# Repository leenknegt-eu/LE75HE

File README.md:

# LE75HE

LE75HE is a 75-key Hall-effect keyboard PCB in the XD75 form factor (15 × 5 grid, all 1U), running [libhmk](https://github.com/peppapighs/libhmk) firmware with 8 kHz polling.

## Status

- Work in progress. PCB and plate are routed but **not yet fabricated or verified**.
- Firmware definition is generated from the PCB netlist and passes the libhmk schema check; it is untested on hardware.

## Layout

Alphanumerics and modifiers sit in the left (columns 1–6) and right (columns 10–15) blocks. The three centre columns hold `-` `` ` `` `=`, `[` `\` `]`, Home/Del/PgUp, End/↑/PgDn and ←/↓/→. Source: [`keyboard-layout.json`](keyboard-layout.json) ([keyboard-layout-editor.com](http://www.keyboard-layout-editor.com)).

### Fn layer (default)

| Key        | Fn            | Key           | Fn                 |
| ---------- | ------------- | ------------- | ------------------ |
| 1–5, 6–0   | F1–F5, F6–F10 | Home / Del / PgUp | Ins / – / Vol+ |
| `-` / `=`  | F11 / F12     | ↑ / PgDn      | Mute / Vol−        |
| Backspace  | Delete        | ← / ↓ / →     | Prev / Play / Next |
| `[` `\` `]`| PrtSc / ScrLk / Pause | U / I / O / P | Profile 0–3 |
| `'`        | Bootloader    | Enter         | Profile swap       |

Layers 2–3 are empty. Everything is remappable in [hmkconf](https://hmk.prasertsuk.com) without reflashing.

## Hardware

| Function        | Part                         | Designator |
| --------------- | ---------------------------- | ---------- |
| MCU             | AT32F405RCT7 (LQFP-64)       | U4         |
| Crystal         | 12 MHz, X322512MSB4SI, 2 × 30 pF | Y1, C152, C153 |
| Hall sensors    | 75 × DRV5055A3 (SOT-23-3), see below | HE1–HE75 |
| Analog muxes    | 10 × SN74LV4051A (TSSOP-16)  | AM1–AM10   |
| LDO, digital    | TLV75733PDYDR, 3.3 V         | U6 (+3.3V) |
| LDO, analog     | TLV75733PDYDR, 3.3 V         | U5 (+3.3VA, sensors + muxes) |
| USB-C           | HRO TYPE-C-31-M-12, CC 2 × 5.1 kΩ | J1, R1, R2 |
| Alt. USB input  | JST SH 1.0 mm 4-pin (VBUS, D−, D+, GND) | J2 |
| ESD             | USBLC6-2SC6                  | U1         |
| Fuse            | BSMD0805-050-24V (500 mA hold) | F1       |
| Reset / Boot    | TS-1187A tactile switches    | SW1 (NRST), SW2 (BOOT0) |
| BOOT0 pull-down | 12 kΩ                        | R4         |
| USB HS bias     | 12 kΩ to GND on OTGHS1_R     | R3         |

- PCB: approx. 285 × 94 mm, switches on 19.05 mm pitch.
- Mounting: 10 × M2 holes (2.2 mm drill).
- Plate: [`plate.dxf`](plate.dxf) in [`plate/`](plate/).
- J1 and J2 share the same USB lines; populate only one.
- Important note: a 500mA hold polyfuse is only applicable for applications using the DRV5055A3 hall sensor. If for example the MT9102ET is used a 750mA - 800mA hold polyfuse is required.

### Case compatibility

- **Gasket mount**: recommended. Should work in 60% gasket-mount cases, as the plate and PCB are held by the gaskets, not the screw holes.
- **Tray mount**: unlikely to work with most 60% cases. The mounting hole layout does not match standard 60% (GH60) tray positions.
- Verify USB-C position and plate fit against the specific case before ordering.

### Pin assignment (U4)

| Signal         | MCU pin     | Connected to |
| -------------- | ----------- | ------------ |
| MUX_SELECT_0   | PC1 (9)     | AM1–AM10 A (11) |
| MUX_SELECT_1   | PC2 (10)    | AM1–AM10 B (10) |
| MUX_SELECT_2   | PC3 (11)    | AM1–AM10 C (9)  |
| MUX_OUT_1      | PA3 (17)    | AM1 X  — HE1–HE8 |
| MUX_OUT_2      | PA4 (20)    | AM2 X  — HE9–HE15 |
| MUX_OUT_3      | PA5 (21)    | AM3 X  — HE16–HE22 |
| MUX_OUT_4      | PA6 (22)    | AM4 X  — HE23–HE30 |
| MUX_OUT_5      | PA7 (23)    | AM5 X  — HE31–HE38 |
| MUX_OUT_6      | PC4 (24)    | AM6 X  — HE39–HE45 |
| MUX_OUT_7      | PC5 (25)    | AM7 X  — HE46–HE49, HE61–HE64 |
| MUX_OUT_8      | PB0 (26)    | AM8 X  — HE50–HE53, HE65–HE68 |
| MUX_OUT_9      | PB1 (27)    | AM9 X  — HE54–HE57, HE69–HE72 |
| MUX_OUT_10     | PA2 (16)    | AM10 X — HE58–HE60, HE73–HE75 |
| HEXT_IN / OUT  | PF0 (5) / PF1 (6) | Y1 |
| USB D− / D+    | OTGHS1_D− (34) / D+ (35) | U1 → J1 / J2 |
| OTGHS1_R       | 33          | R3 |
| BOOT0          | PF11 (60)   | SW2, R4 |
| NRST           | 7           | SW1 |

Sensor `HEn` sits under key `n`, counted row-major from the top-left; firmware key index is `n − 1`. The exact channel mapping is in [`firmware/le75he/keyboard.json`](firmware/le75he/keyboard.json). Unused mux channels (AM2 X3, AM3 X6, AM6 X3, AM10 X3, AM10 X5) are tied to GND.

### Hall-effect sensor

**Recommended: DRV5055A3** (Texas Instruments, SOT-23 `DBZ` package).

- Drop-in: SOT-23 pinout is 1 VCC, 2 OUT, 3 GND, matching the footprint. The schematic/PCB still carry the value `MT9102ET`; select DRV5055A3 instead at assembly.
- Lower supply current: 2 mA typ / 4 mA max at 3.3 V, i.e. ~150 mA typ for 75 sensors on the analog LDO (U5).
- Sensitivity ≈ 15 mV/mT at 3.3 V (±85 mT range), close to MT9102ET (≈ 16 mV/mT), so the firmware's default calibration applies to both.
- Decoupling: the existing 100 nF per sensor on VCC meets TI's 10 nF minimum.
- **Output capacitor: do not populate (DNP) the 4.7 nF capacitor on each `HEn` net when fitting DRV5055A3.** On this PCB it connects directly from sensor OUT to GND with no series resistor. TI states a capacitor must not be connected directly to the DRV5055 output without a resistor in between, as the output can become unstable. Without it, the sensor drives the mux/ADC directly; libhmk filters the readings in firmware.

#### Assembly by sensor

Each key has two 0402 capacitors: 100 nF from +3.3VA to GND (sensor supply) and 4.7 nF from `HEn` (sensor OUT) to GND. The 4.7 nF parts are the only 4.7 nF capacitors on the board (75 pcs).

| Sensor | Part number (HE1–HE75) | 100 nF supply caps | 4.7 nF output caps | Firmware |
| ------ | ---------------------- | ------------------ | ------------------ | -------- |
| DRV5055A3 (recommended) | DRV5055A3QDBZR | Populate | **DNP** | No change |
| MT9102ET | MT9102ET | Populate | Populate | No change |

- **MT9102ET:** the board as drawn. The MT9102 datasheet allows up to 10 nF output load to GND and its reference circuit uses 100 nF on VCC plus an output capacitor directly to GND, so 4.7 nF is within spec.
- **DRV5055A3:** replace the sensor part in the BOM and exclude the 4.7 nF capacitors from assembly:
  1. In the fab's BOM/component selection, swap `MT9102ET` for `DRV5055A3QDBZR` on HE1–HE75.
  2. Deselect (do not place) every 4.7 nF 0402 capacitor.
  3. Alternatively in KiCad: Schematic Editor → *Symbol Fields Table*, filter Value `4.7n`, tick **DNP** for all 75 rows, then set `"EXCLUDE DNP": true` in `HE75/fabrication-toolkit-options.json` before generating production files.
- Mixing sensor types on one board is not recommended; both work with the same default calibration, but per-key travel will differ slightly.

Other linear ratiometric 3.3 V Hall sensors in SOT-23-3 with the same pinout (VCC, OUT, GND) can be substituted. Check the pinout first; calibration may need adjusting in hmkconf. Known options:

- DRV5055A3 (recommended)
- MT9102ET (schematic value)
- GH39FKSW
- SS39ET
- OH49E-S (discontinued)

## Firmware

The libhmk keyboard definition is in [`firmware/le75he/`](firmware/le75he/). Summary:

- Driver `at32f405xx`, HSE 12 MHz, USB high-speed port.
- 75 keys, 4 profiles, 4 layers, 32 advanced keys.
- Mux select `C1, C2, C3`; ADC inputs `A3, A4, A5, A6, A7, C4, C5, B0, B1, A2`.
- Calibration defaults (DRV5055A3 / MT9102ET): rest 2400, bottom-out threshold 650, ADC not inverted. Auto-calibration refines these per key at runtime.

Build:

```bash
git clone https://github.com/peppapighs/libhmk.git
```

```bash
cp -r firmware/le75he libhmk/keyboards/
```

```bash
cd libhmk && python setup.py -k le75he && pio run
```

Flash `.pio/build/le75he/firmware.bin` over DFU: hold **BOOT** (SW2) while plugging in, then use [WebUSB DFU](https://devanlai.github.io/webdfu/dfu-util/) or `pio run --target upload`. On Windows the DFU driver may need to be installed with Zadig.

## Repository

| Path                   | Content |
| ---------------------- | ------- |
| `HE75/`                | KiCad PCB project (schematic, layout, footprint/symbol libraries) |
| `plate/`, `plate.dxf`  | Switch plate |
| `firmware/le75he/`     | libhmk keyboard definition |
| `keyboard-layout.json` | Layout source (KLE) |
| `doc/layout.svg`       | Layout image |

## Credits

Derived from [peppapighs/HE60](https://github.com/peppapighs/HE60). Licensed under GPL-3.0, see [LICENSE](LICENSE).

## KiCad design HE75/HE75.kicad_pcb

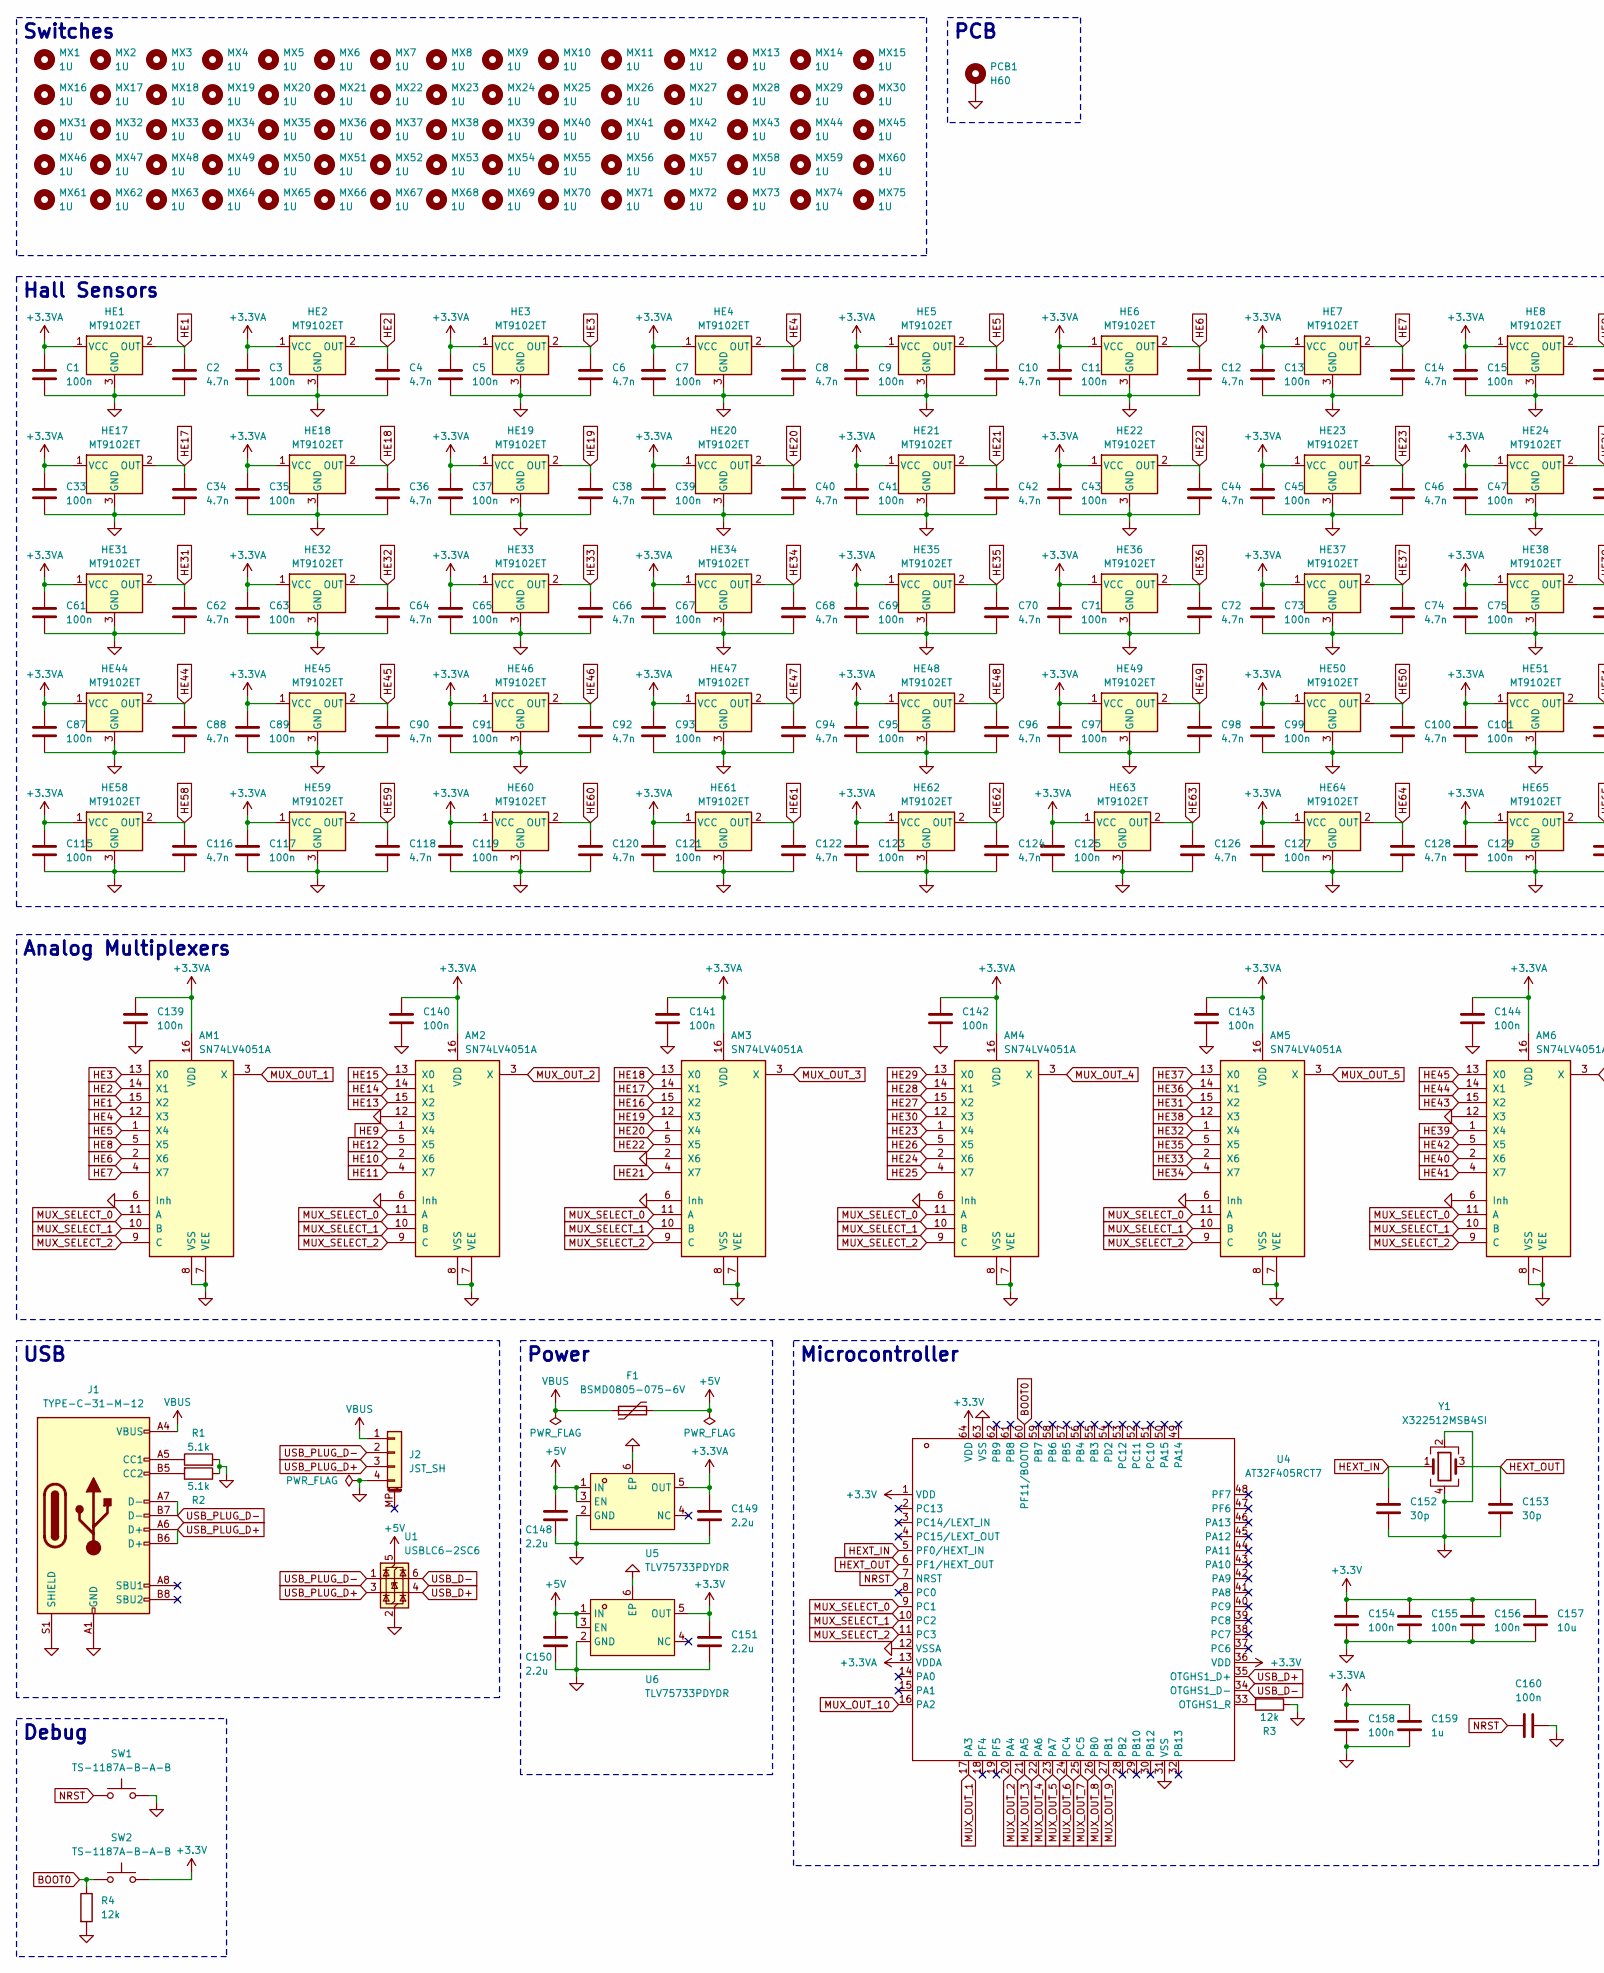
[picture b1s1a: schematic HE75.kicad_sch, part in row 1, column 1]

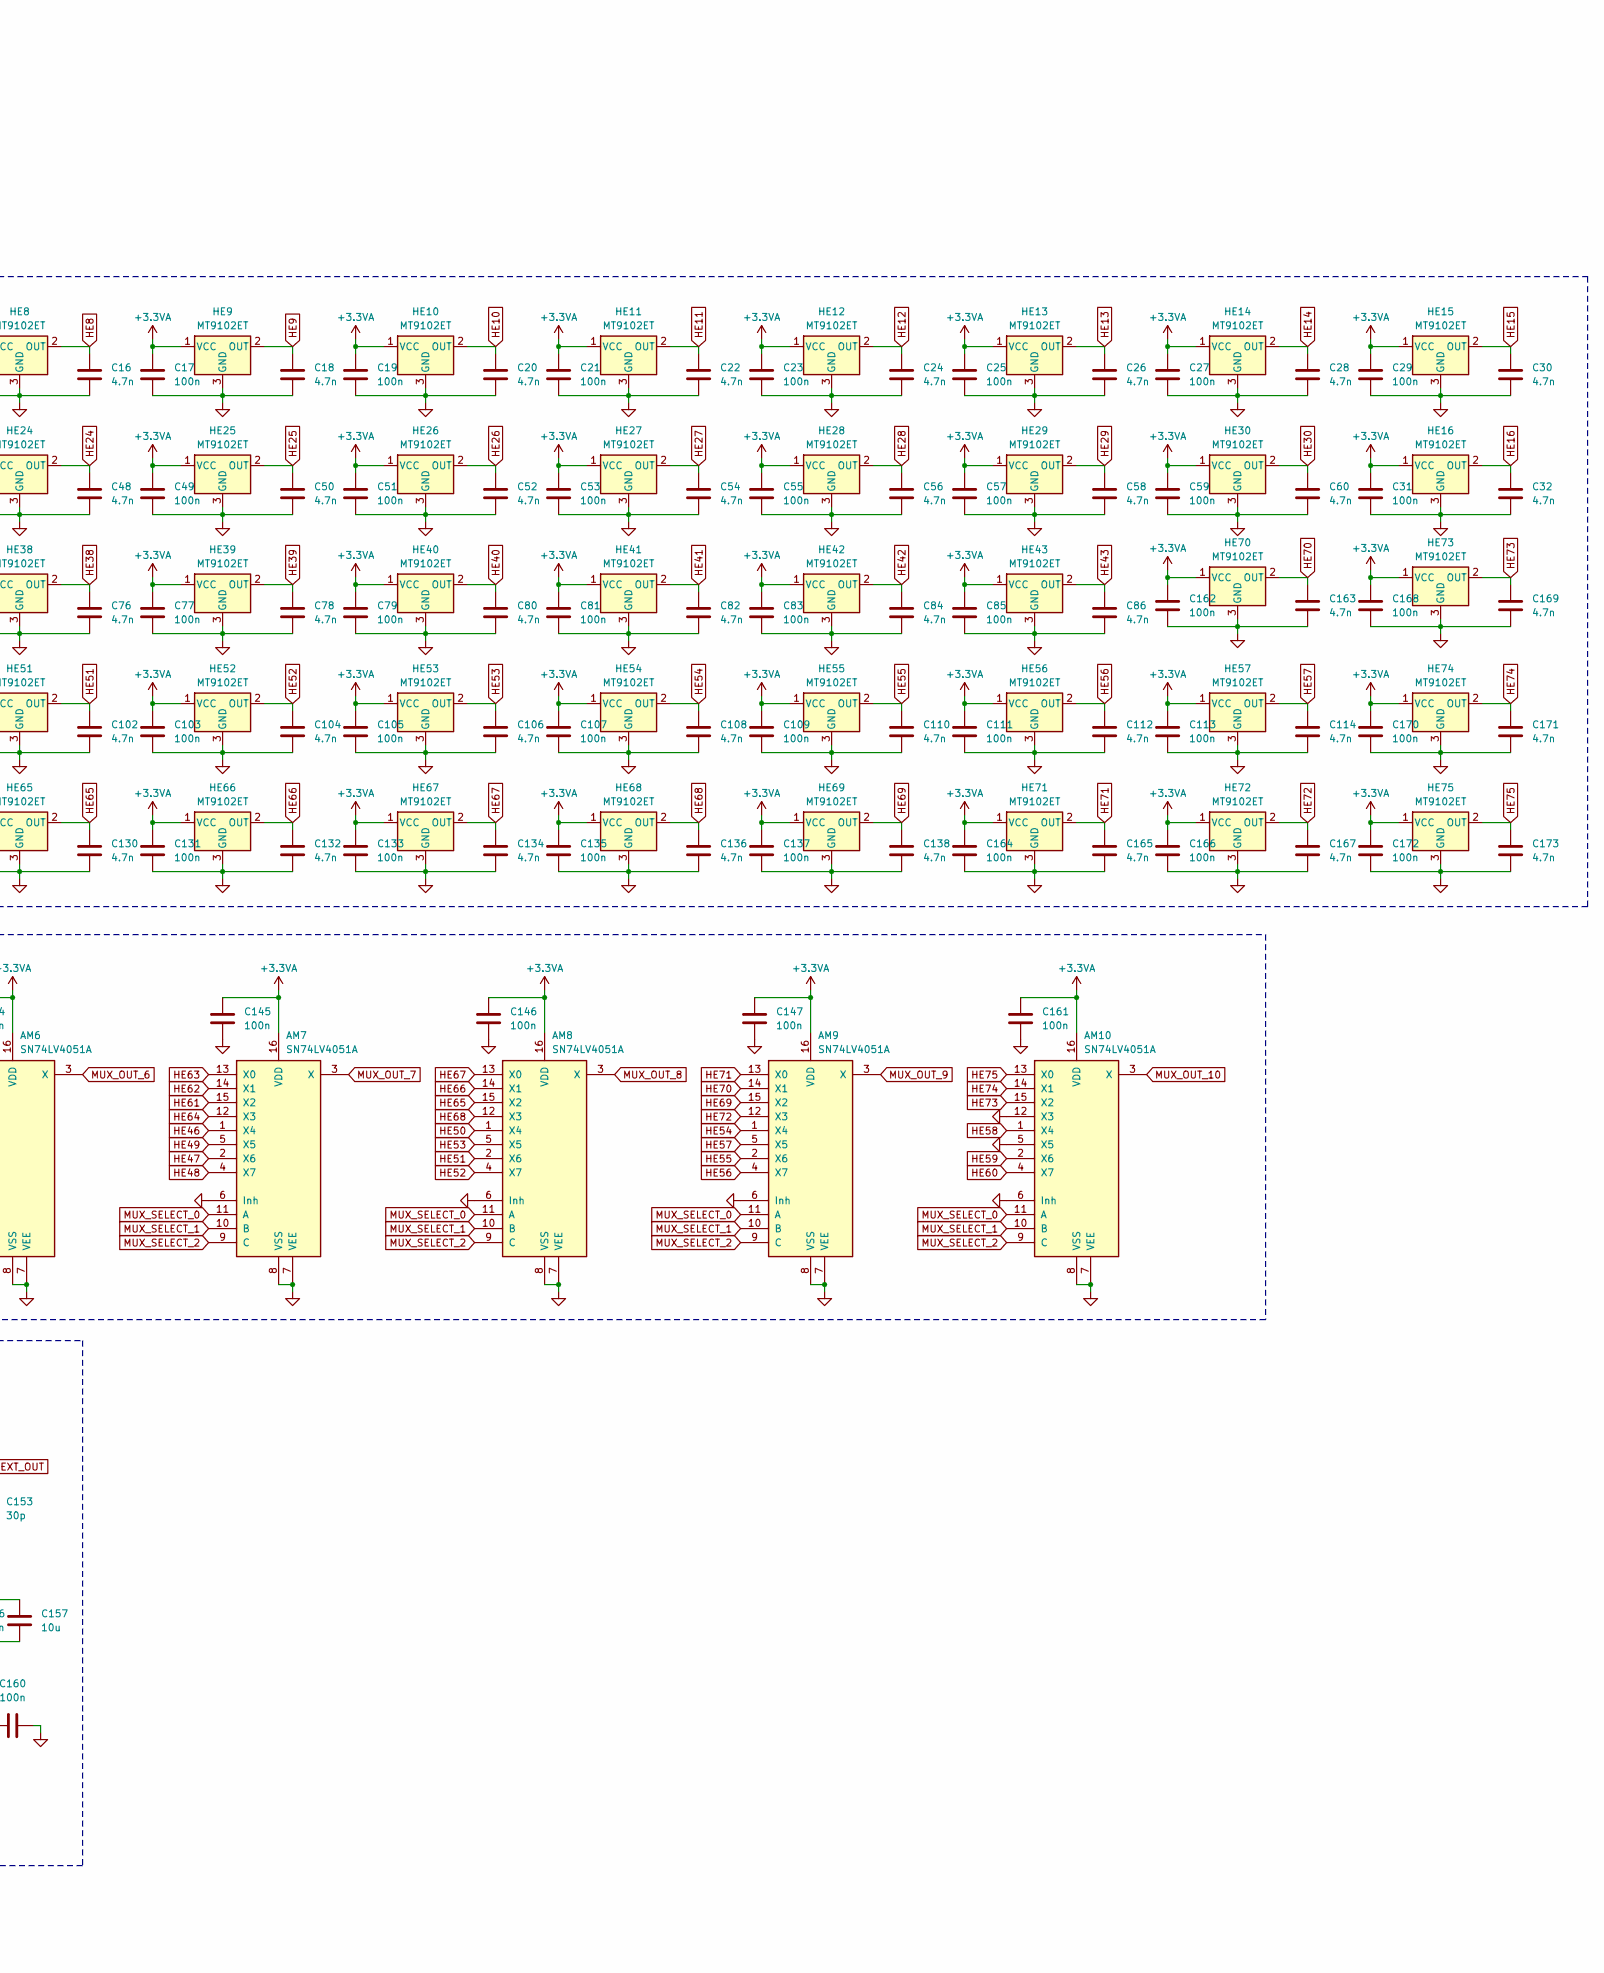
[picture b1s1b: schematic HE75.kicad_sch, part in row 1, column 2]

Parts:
AM1, AM2, AM3, AM4, AM5, AM6, AM7, AM8, AM9, AM10: SN74LV4051A; TSSOP-16_4.4x5mm_P0.65mm
C1, C3, C5, C7, C9, C11, C13, C15, C17, C19, C21, C23, C25, C27, C29, C31, C33, C35, C37, C39, C41, C43, C45, C47, C49, C51, C53, C55, C57, C59, C61, C63, C65, C67, C69, C71, C73, C75, C77, C79, C81, C83, C85, C87, C89, C91, C93, C95, C97, C99, C101, C103, C105, C107, C109, C111, C113, C115, C117, C119, C121, C123, C125, C127, C129, C131, C133, C135, C137, C139, C140, C141, C142, C143, C144, C145, C146, C147, C154, C155, C156, C158, C160, C161, C162, C164, C166, C168, C170, C172: 100n; C_0402_1005Metric
C2, C4, C6, C8, C10, C12, C14, C16, C18, C20, C22, C24, C26, C28, C30, C32, C34, C36, C38, C40, C42, C44, C46, C48, C50, C52, C54, C56, C58, C60, C62, C64, C66, C68, C70, C72, C74, C76, C78, C80, C82, C84, C86, C88, C90, C92, C94, C96, C98, C100, C102, C104, C106, C108, C110, C112, C114, C116, C118, C120, C122, C124, C126, C128, C130, C132, C134, C136, C138, C163, C165, C167, C169, C171, C173: 4.7n; C_0402_1005Metric
C148, C149, C150, C151: 2.2u; C_0603_1608Metric
C152, C153: 30p; C_0603_1608Metric
C157: 10u; C_0603_1608Metric
C159: 1u; C_0603_1608Metric
F1: BSMD0805-075-6V; Fuse_0805_2012Metric
HE1, HE2, HE3, HE4, HE5, HE6, HE7, HE8, HE9, HE10, HE11, HE12, HE13, HE14, HE15, HE16, HE17, HE18, HE19, HE20, HE21, HE22, HE23, HE24, HE25, HE26, HE27, HE28, HE29, HE30, HE31, HE32, HE33, HE34, HE35, HE36, HE37, HE38, HE39, HE40, HE41, HE42, HE43, HE44, HE45, HE46, HE47, HE48, HE49, HE50, HE51, HE52, HE53, HE54, HE55, HE56, HE57, HE58, HE59, HE60, HE61, HE62, HE63, HE64, HE65, HE66, HE67, HE68, HE69, HE70, HE71, HE72, HE73, HE74, HE75: MT9102ET; SOT-23-3
J1: TYPE-C-31-M-12; USB_C_Receptacle_HRO_TYPE-C-31-M-12
J2: JST_SH; JST_SH_SM04B-SRSS-TB_1x04-1MP_P1.00mm_Horizontal
MX1, MX2, MX3, MX4, MX5, MX6, MX7, MX8, MX9, MX10, MX11, MX12, MX13, MX14, MX15, MX16, MX17, MX18, MX19, MX20, MX21, MX22, MX23, MX24, MX25, MX26, MX27, MX28, MX29, MX30, MX31, MX32, MX33, MX34, MX35, MX36, MX37, MX38, MX39, MX40, MX41, MX42, MX43, MX44, MX45, MX46, MX47, MX48, MX49, MX50, MX51, MX52, MX53, MX54, MX55, MX56, MX57, MX58, MX59, MX60, MX61, MX62, MX63, MX64, MX65, MX66, MX67, MX68, MX69, MX70, MX71, MX72, MX73, MX74, MX75: 1U; MX-1U
PCB1: H60
R1, R2: 5.1k; R_0402_1005Metric
R3, R4: 12k; R_0402_1005Metric
SW1, SW2: TS-1187A-B-A-B; SW_Push_1P1T_XKB_TS-1187A
U1: USBLC6-2SC6; SOT-23-6
U4: AT32F405RCT7; LQFP-64_10x10mm_P0.5mm
U5, U6: TLV75733PDYDR; SOT-23-5_L2.9-W1.6-P0.95-LS2.8-BL-EP; MPN TLV75733PDYDR; LCSC Part C22399950
Y1: X322512MSB4SI; Crystal_SMD_3225-4Pin_3.2x2.5mm

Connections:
+3.3V: C151.1, C154.1, C155.1, C156.1, C157.1, SW2.2, U4.1 (VDD), U4.36 (VDD), U4.64 (VDD), U6.5 (OUT)
+3.3VA: AM1.16 (VDD), AM2.16 (VDD), AM3.16 (VDD), AM4.16 (VDD), AM5.16 (VDD), AM6.16 (VDD), AM7.16 (VDD), AM8.16 (VDD), AM9.16 (VDD), AM10.16 (VDD), C1.1, C3.1, C5.1, C7.1, C9.1, C11.1, C13.1, C15.1, C17.1, C19.1, C21.1, C23.1, C25.1, C27.1, C29.1, C31.1, C33.1, C35.1, C37.1, C39.1, C41.1, C43.1, C45.1, C47.1, C49.1, C51.1, C53.1, C55.1, C57.1, C59.1, C61.1, C63.1, C65.1, C67.1, C69.1, C71.1, C73.1, C75.1, C77.1, C79.1, C81.1, C83.1, C85.1, C87.1, C89.1, C91.1, C93.1, C95.1, C97.1, C99.1, C101.1, C103.1, C105.1, C107.1, C109.1, C111.1, C113.1, C115.1, C117.1, C119.1, C121.1, C123.1, C125.1, C127.1, C129.1, C131.1, C133.1, C135.1, C137.1, C139.1, C140.1, C141.1, C142.1, C143.1, C144.1, C145.1, C146.1, C147.1, C149.1, C158.1, C159.1, C161.1, C162.1, C164.1, C166.1, C168.1, C170.1, C172.1, HE1.1 (VCC), HE2.1 (VCC), HE3.1 (VCC), HE4.1 (VCC), HE5.1 (VCC), HE6.1 (VCC), HE7.1 (VCC), HE8.1 (VCC), HE9.1 (VCC), HE10.1 (VCC), HE11.1 (VCC), HE12.1 (VCC), HE13.1 (VCC), HE14.1 (VCC), HE15.1 (VCC), HE16.1 (VCC), HE17.1 (VCC), HE18.1 (VCC), HE19.1 (VCC), HE20.1 (VCC), HE21.1 (VCC), HE22.1 (VCC), HE23.1 (VCC), HE24.1 (VCC), HE25.1 (VCC), HE26.1 (VCC), HE27.1 (VCC), HE28.1 (VCC), HE29.1 (VCC), HE30.1 (VCC), HE31.1 (VCC), HE32.1 (VCC), HE33.1 (VCC), HE34.1 (VCC), HE35.1 (VCC), HE36.1 (VCC), HE37.1 (VCC), HE38.1 (VCC), HE39.1 (VCC), HE40.1 (VCC), HE41.1 (VCC), HE42.1 (VCC), HE43.1 (VCC), HE44.1 (VCC), HE45.1 (VCC), HE46.1 (VCC), HE47.1 (VCC), HE48.1 (VCC), HE49.1 (VCC), HE50.1 (VCC), HE51.1 (VCC), HE52.1 (VCC), HE53.1 (VCC), HE54.1 (VCC), HE55.1 (VCC), HE56.1 (VCC), HE57.1 (VCC), HE58.1 (VCC), HE59.1 (VCC), HE60.1 (VCC), HE61.1 (VCC), HE62.1 (VCC), HE63.1 (VCC), HE64.1 (VCC), HE65.1 (VCC), HE66.1 (VCC), HE67.1 (VCC), HE68.1 (VCC), HE69.1 (VCC), HE70.1 (VCC), HE71.1 (VCC), HE72.1 (VCC), HE73.1 (VCC), HE74.1 (VCC), HE75.1 (VCC), U4.13 (VDDA), U5.5 (OUT)
+5V: C148.1, C150.1, F1.2, U1.5 (VBUS), U5.1 (IN), U5.3 (EN), U6.1 (IN), U6.3 (EN)
BOOT0: R4.1, SW2.1, U4.60 (PF11/BOOT0)
GND: AM1.6 (Inh), AM1.7 (VEE), AM1.8 (VSS), AM2.6 (Inh), AM2.7 (VEE), AM2.8 (VSS), AM2.12 (X3), AM3.2 (X6), AM3.6 (Inh), AM3.7 (VEE), AM3.8 (VSS), AM4.6 (Inh), AM4.7 (VEE), AM4.8 (VSS), AM5.6 (Inh), AM5.7 (VEE), AM5.8 (VSS), AM6.6 (Inh), AM6.7 (VEE), AM6.8 (VSS), AM6.12 (X3), AM7.6 (Inh), AM7.7 (VEE), AM7.8 (VSS), AM8.6 (Inh), AM8.7 (VEE), AM8.8 (VSS), AM9.6 (Inh), AM9.7 (VEE), AM9.8 (VSS), AM10.5 (X5), AM10.6 (Inh), AM10.7 (VEE), AM10.8 (VSS), AM10.12 (X3), C1.2, C2.2, C3.2, C4.2, C5.2, C6.2, C7.2, C8.2, C9.2, C10.2, C11.2, C12.2, C13.2, C14.2, C15.2, C16.2, C17.2, C18.2, C19.2, C20.2, C21.2, C22.2, C23.2, C24.2, C25.2, C26.2, C27.2, C28.2, C29.2, C30.2, C31.2, C32.2, C33.2, C34.2, C35.2, C36.2, C37.2, C38.2, C39.2, C40.2, C41.2, C42.2, C43.2, C44.2, C45.2, C46.2, C47.2, C48.2, C49.2, C50.2, C51.2, C52.2, C53.2, C54.2, C55.2, C56.2, C57.2, C58.2, C59.2, C60.2, C61.2, C62.2, C63.2, C64.2, C65.2, C66.2, C67.2, C68.2, C69.2, C70.2, C71.2, C72.2, C73.2, C74.2, C75.2, C76.2, C77.2, C78.2, C79.2, C80.2, C81.2, C82.2, C83.2, C84.2, C85.2, C86.2, C87.2, C88.2, C89.2, C90.2, C91.2, C92.2, C93.2, C94.2, C95.2, C96.2, C97.2, C98.2, C99.2, C100.2, C101.2, C102.2, C103.2, C104.2, C105.2, C106.2, C107.2, C108.2, C109.2, C110.2, C111.2, C112.2, C113.2, C114.2, C115.2, C116.2, C117.2, C118.2, C119.2, C120.2, C121.2, C122.2, C123.2, C124.2, C125.2, C126.2, C127.2, C128.2, C129.2, C130.2, C131.2, C132.2, C133.2, C134.2, C135.2, C136.2, C137.2, C138.2, C139.2, C140.2, C141.2, C142.2, C143.2, C144.2, C145.2, C146.2, C147.2, C148.2, C149.2, C150.2, C151.2, C152.2, C153.2, C154.2, C155.2, C156.2, C157.2, C158.2, C159.2, C160.2, C161.2, C162.2, C163.2, C164.2, C165.2, C166.2, C167.2, C168.2, C169.2, C170.2, C171.2, C172.2, C173.2, HE1.3 (GND), HE2.3 (GND), HE3.3 (GND), HE4.3 (GND), HE5.3 (GND), HE6.3 (GND), HE7.3 (GND), HE8.3 (GND), HE9.3 (GND), HE10.3 (GND), HE11.3 (GND), HE12.3 (GND), HE13.3 (GND), HE14.3 (GND), HE15.3 (GND), HE16.3 (GND), HE17.3 (GND), HE18.3 (GND), HE19.3 (GND), HE20.3 (GND), HE21.3 (GND), HE22.3 (GND), HE23.3 (GND), HE24.3 (GND), HE25.3 (GND), HE26.3 (GND), HE27.3 (GND), HE28.3 (GND), HE29.3 (GND), HE30.3 (GND), HE31.3 (GND), HE32.3 (GND), HE33.3 (GND), HE34.3 (GND), HE35.3 (GND), HE36.3 (GND), HE37.3 (GND), HE38.3 (GND), HE39.3 (GND), HE40.3 (GND), HE41.3 (GND), HE42.3 (GND), HE43.3 (GND), HE44.3 (GND), HE45.3 (GND), HE46.3 (GND), HE47.3 (GND), HE48.3 (GND), HE49.3 (GND), HE50.3 (GND), HE51.3 (GND), HE52.3 (GND), HE53.3 (GND), HE54.3 (GND), HE55.3 (GND), HE56.3 (GND), HE57.3 (GND), HE58.3 (GND), HE59.3 (GND), HE60.3 (GND), HE61.3 (GND), HE62.3 (GND), HE63.3 (GND), HE64.3 (GND), HE65.3 (GND), HE66.3 (GND), HE67.3 (GND), HE68.3 (GND), HE69.3 (GND), HE70.3 (GND), HE71.3 (GND), HE72.3 (GND), HE73.3 (GND), HE74.3 (GND), HE75.3 (GND), J1.A1 (GND), J1.A12 (GND), J1.B1 (GND), J1.B12 (GND), J1.S1 (SHIELD), J2.4, PCB1.1, R1.2, R2.1, R3.1, R4.2, SW1.2, U1.2 (GND), U4.12 (VSSA), U4.31 (VSS), U4.63 (VSS), U5.2 (GND), U5.6 (EP), U6.2 (GND), U6.6 (EP), Y1.2, Y1.4
HE1: AM1.15 (X2), C2.1, HE1.2 (OUT)
HE2: AM1.14 (X1), C4.1, HE2.2 (OUT)
HE3: AM1.13 (X0), C6.1, HE3.2 (OUT)
HE4: AM1.12 (X3), C8.1, HE4.2 (OUT)
HE5: AM1.1 (X4), C10.1, HE5.2 (OUT)
HE6: AM1.2 (X6), C12.1, HE6.2 (OUT)
HE7: AM1.4 (X7), C14.1, HE7.2 (OUT)
HE8: AM1.5 (X5), C16.1, HE8.2 (OUT)
HE9: AM2.1 (X4), C18.1, HE9.2 (OUT)
HE10: AM2.2 (X6), C20.1, HE10.2 (OUT)
HE11: AM2.4 (X7), C22.1, HE11.2 (OUT)
HE12: AM2.5 (X5), C24.1, HE12.2 (OUT)
HE13: AM2.15 (X2), C26.1, HE13.2 (OUT)
HE14: AM2.14 (X1), C28.1, HE14.2 (OUT)
HE15: AM2.13 (X0), C30.1, HE15.2 (OUT)
HE16: AM3.15 (X2), C32.1, HE16.2 (OUT)
HE17: AM3.14 (X1), C34.1, HE17.2 (OUT)
HE18: AM3.13 (X0), C36.1, HE18.2 (OUT)
HE19: AM3.12 (X3), C38.1, HE19.2 (OUT)
HE20: AM3.1 (X4), C40.1, HE20.2 (OUT)
HE21: AM3.4 (X7), C42.1, HE21.2 (OUT)
HE22: AM3.5 (X5), C44.1, HE22.2 (OUT)
HE23: AM4.1 (X4), C46.1, HE23.2 (OUT)
HE24: AM4.2 (X6), C48.1, HE24.2 (OUT)
HE25: AM4.4 (X7), C50.1, HE25.2 (OUT)
HE26: AM4.5 (X5), C52.1, HE26.2 (OUT)
HE27: AM4.15 (X2), C54.1, HE27.2 (OUT)
HE28: AM4.14 (X1), C56.1, HE28.2 (OUT)
HE29: AM4.13 (X0), C58.1, HE29.2 (OUT)
HE30: AM4.12 (X3), C60.1, HE30.2 (OUT)
HE31: AM5.15 (X2), C62.1, HE31.2 (OUT)
HE32: AM5.1 (X4), C64.1, HE32.2 (OUT)
HE33: AM5.2 (X6), C66.1, HE33.2 (OUT)
HE34: AM5.4 (X7), C68.1, HE34.2 (OUT)
HE35: AM5.5 (X5), C70.1, HE35.2 (OUT)
HE36: AM5.14 (X1), C72.1, HE36.2 (OUT)
HE37: AM5.13 (X0), C74.1, HE37.2 (OUT)
HE38: AM5.12 (X3), C76.1, HE38.2 (OUT)
HE39: AM6.1 (X4), C78.1, HE39.2 (OUT)
HE40: AM6.2 (X6), C80.1, HE40.2 (OUT)
HE41: AM6.4 (X7), C82.1, HE41.2 (OUT)
HE42: AM6.5 (X5), C84.1, HE42.2 (OUT)
HE43: AM6.15 (X2), C86.1, HE43.2 (OUT)
HE44: AM6.14 (X1), C88.1, HE44.2 (OUT)
HE45: AM6.13 (X0), C90.1, HE45.2 (OUT)
HE46: AM7.1 (X4), C92.1, HE46.2 (OUT)
HE47: AM7.2 (X6), C94.1, HE47.2 (OUT)
HE48: AM7.4 (X7), C96.1, HE48.2 (OUT)
HE49: AM7.5 (X5), C98.1, HE49.2 (OUT)
HE50: AM8.1 (X4), C100.1, HE50.2 (OUT)
HE51: AM8.2 (X6), C102.1, HE51.2 (OUT)
HE52: AM8.4 (X7), C104.1, HE52.2 (OUT)
HE53: AM8.5 (X5), C106.1, HE53.2 (OUT)
HE54: AM9.1 (X4), C108.1, HE54.2 (OUT)
HE55: AM9.2 (X6), C110.1, HE55.2 (OUT)
HE56: AM9.4 (X7), C112.1, HE56.2 (OUT)
HE57: AM9.5 (X5), C114.1, HE57.2 (OUT)
HE58: AM10.1 (X4), C116.1, HE58.2 (OUT)
HE59: AM10.2 (X6), C118.1, HE59.2 (OUT)
HE60: AM10.4 (X7), C120.1, HE60.2 (OUT)
HE61: AM7.15 (X2), C122.1, HE61.2 (OUT)
HE62: AM7.14 (X1), C124.1, HE62.2 (OUT)
HE63: AM7.13 (X0), C126.1, HE63.2 (OUT)
HE64: AM7.12 (X3), C128.1, HE64.2 (OUT)
HE65: AM8.15 (X2), C130.1, HE65.2 (OUT)
HE66: AM8.14 (X1), C132.1, HE66.2 (OUT)
HE67: AM8.13 (X0), C134.1, HE67.2 (OUT)
HE68: AM8.12 (X3), C136.1, HE68.2 (OUT)
HE69: AM9.15 (X2), C138.1, HE69.2 (OUT)
HE70: AM9.14 (X1), C163.1, HE70.2 (OUT)
HE71: AM9.13 (X0), C165.1, HE71.2 (OUT)
HE72: AM9.12 (X3), C167.1, HE72.2 (OUT)
HE73: AM10.15 (X2), C169.1, HE73.2 (OUT)
HE74: AM10.14 (X1), C171.1, HE74.2 (OUT)
HE75: AM10.13 (X0), C173.1, HE75.2 (OUT)
HEXT_IN: C152.1, U4.5 (PF0/HEXT_IN), Y1.1
HEXT_OUT: C153.1, U4.6 (PF1/HEXT_OUT), Y1.3
MUX_OUT_1: AM1.3 (X), U4.17 (PA3)
MUX_OUT_2: AM2.3 (X), U4.20 (PA4)
MUX_OUT_3: AM3.3 (X), U4.21 (PA5)
MUX_OUT_4: AM4.3 (X), U4.22 (PA6)
MUX_OUT_5: AM5.3 (X), U4.23 (PA7)
MUX_OUT_6: AM6.3 (X), U4.24 (PC4)
MUX_OUT_7: AM7.3 (X), U4.25 (PC5)
MUX_OUT_8: AM8.3 (X), U4.26 (PB0)
MUX_OUT_9: AM9.3 (X), U4.27 (PB1)
MUX_OUT_10: AM10.3 (X), U4.16 (PA2)
MUX_SELECT_0: AM1.11 (A), AM2.11 (A), AM3.11 (A), AM4.11 (A), AM5.11 (A), AM6.11 (A), AM7.11 (A), AM8.11 (A), AM9.11 (A), AM10.11 (A), U4.9 (PC1)
MUX_SELECT_1: AM1.10 (B), AM2.10 (B), AM3.10 (B), AM4.10 (B), AM5.10 (B), AM6.10 (B), AM7.10 (B), AM8.10 (B), AM9.10 (B), AM10.10 (B), U4.10 (PC2)
MUX_SELECT_2: AM1.9 (C), AM2.9 (C), AM3.9 (C), AM4.9 (C), AM5.9 (C), AM6.9 (C), AM7.9 (C), AM8.9 (C), AM9.9 (C), AM10.9 (C), U4.11 (PC3)
NRST: C160.1, SW1.1, U4.7 (NRST)
unnamed: J1.A5 (CC1), R1.1
unnamed: J1.B5 (CC2), R2.2
unnamed: R3.2, U4.33 (OTGHS1_R)
USB_D+: U1.4 (I/O2), U4.35 (OTGHS1_D+)
USB_D-: U1.6 (I/O1), U4.34 (OTGHS1_D-)
USB_PLUG_D+: J1.A6 (D+), J1.B6 (D+), J2.3, U1.3 (I/O2)
USB_PLUG_D-: J1.A7 (D-), J1.B7 (D-), J2.2, U1.1 (I/O1)
VBUS: F1.1, J1.A4 (VBUS), J1.A9 (VBUS), J1.B4 (VBUS), J1.B9 (VBUS), J2.1

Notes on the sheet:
PCB
Hall Sensors
Switches
USB
Analog Multiplexers
Power
Debug
Microcontroller

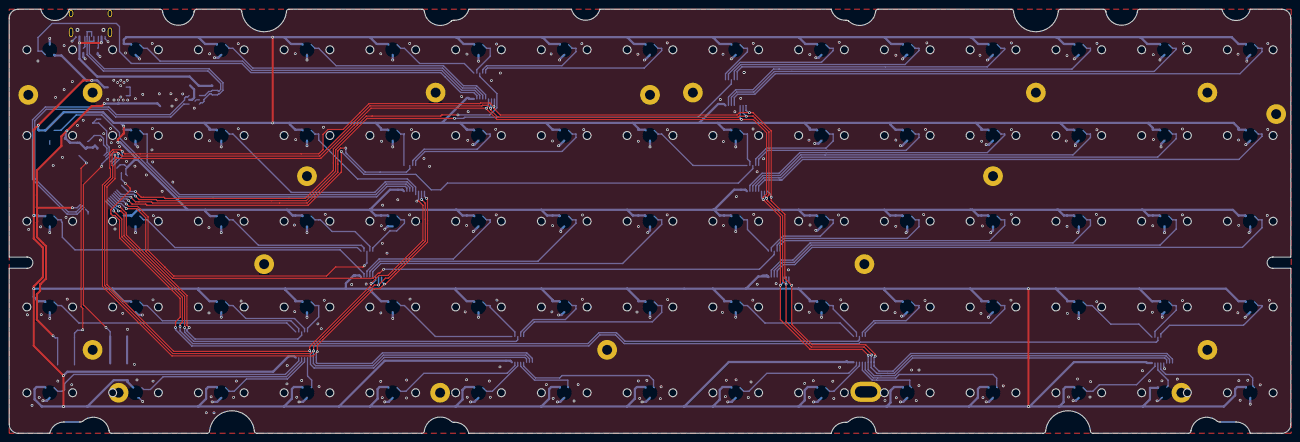
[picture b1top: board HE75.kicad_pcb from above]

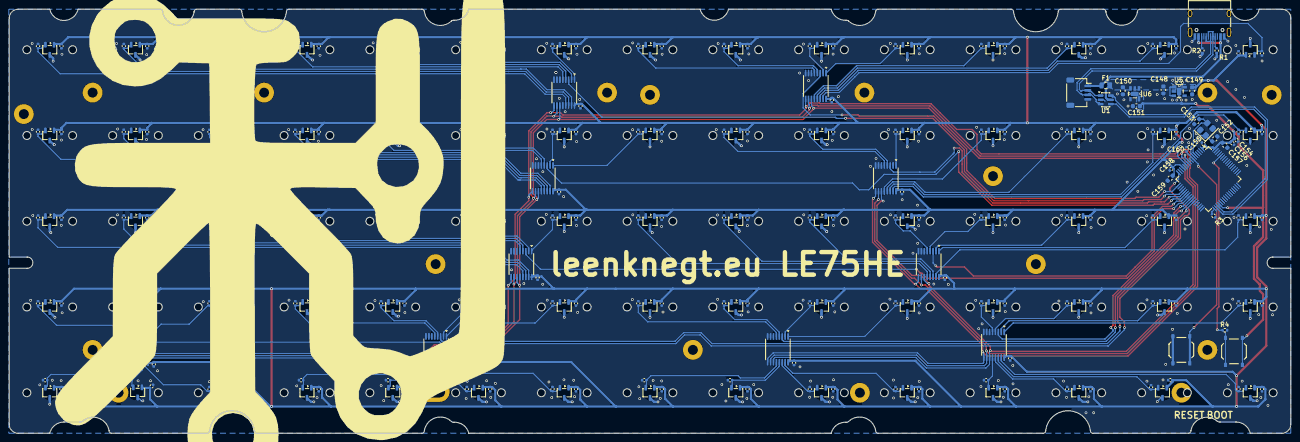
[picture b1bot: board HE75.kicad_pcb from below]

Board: 2 copper layers, 284.7 x 94.2 mm, 348 parts (272 on the bottom side), 104 nets.
